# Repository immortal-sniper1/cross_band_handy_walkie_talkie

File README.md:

# Cross Band Handy Walkie Talkie

A Cross band handy walkie talkie: This HT would include 2 SA818s, one for 70cm and one for 2m and could be used for satellite work.
 
We recommend to install the following libraries:

__Audio__

- https://github.com/pschatzmann/arduino-audio-tools.git
- https://github.com/pschatzmann/arduino-audiokit.git (ES8388 driver for AudioKitStream class)
- https://github.com/thaaraak/es8388 (alternative ES8388 driver)
 
__DRA818__

To use the Transceiver you need an Arduino library. e.g.
- https://github.com/fatpat/arduino-dra818.git

 You can install this project as Arduino Library. To compile a Sketch select the __ESP32S3 Dev Module__ as board.

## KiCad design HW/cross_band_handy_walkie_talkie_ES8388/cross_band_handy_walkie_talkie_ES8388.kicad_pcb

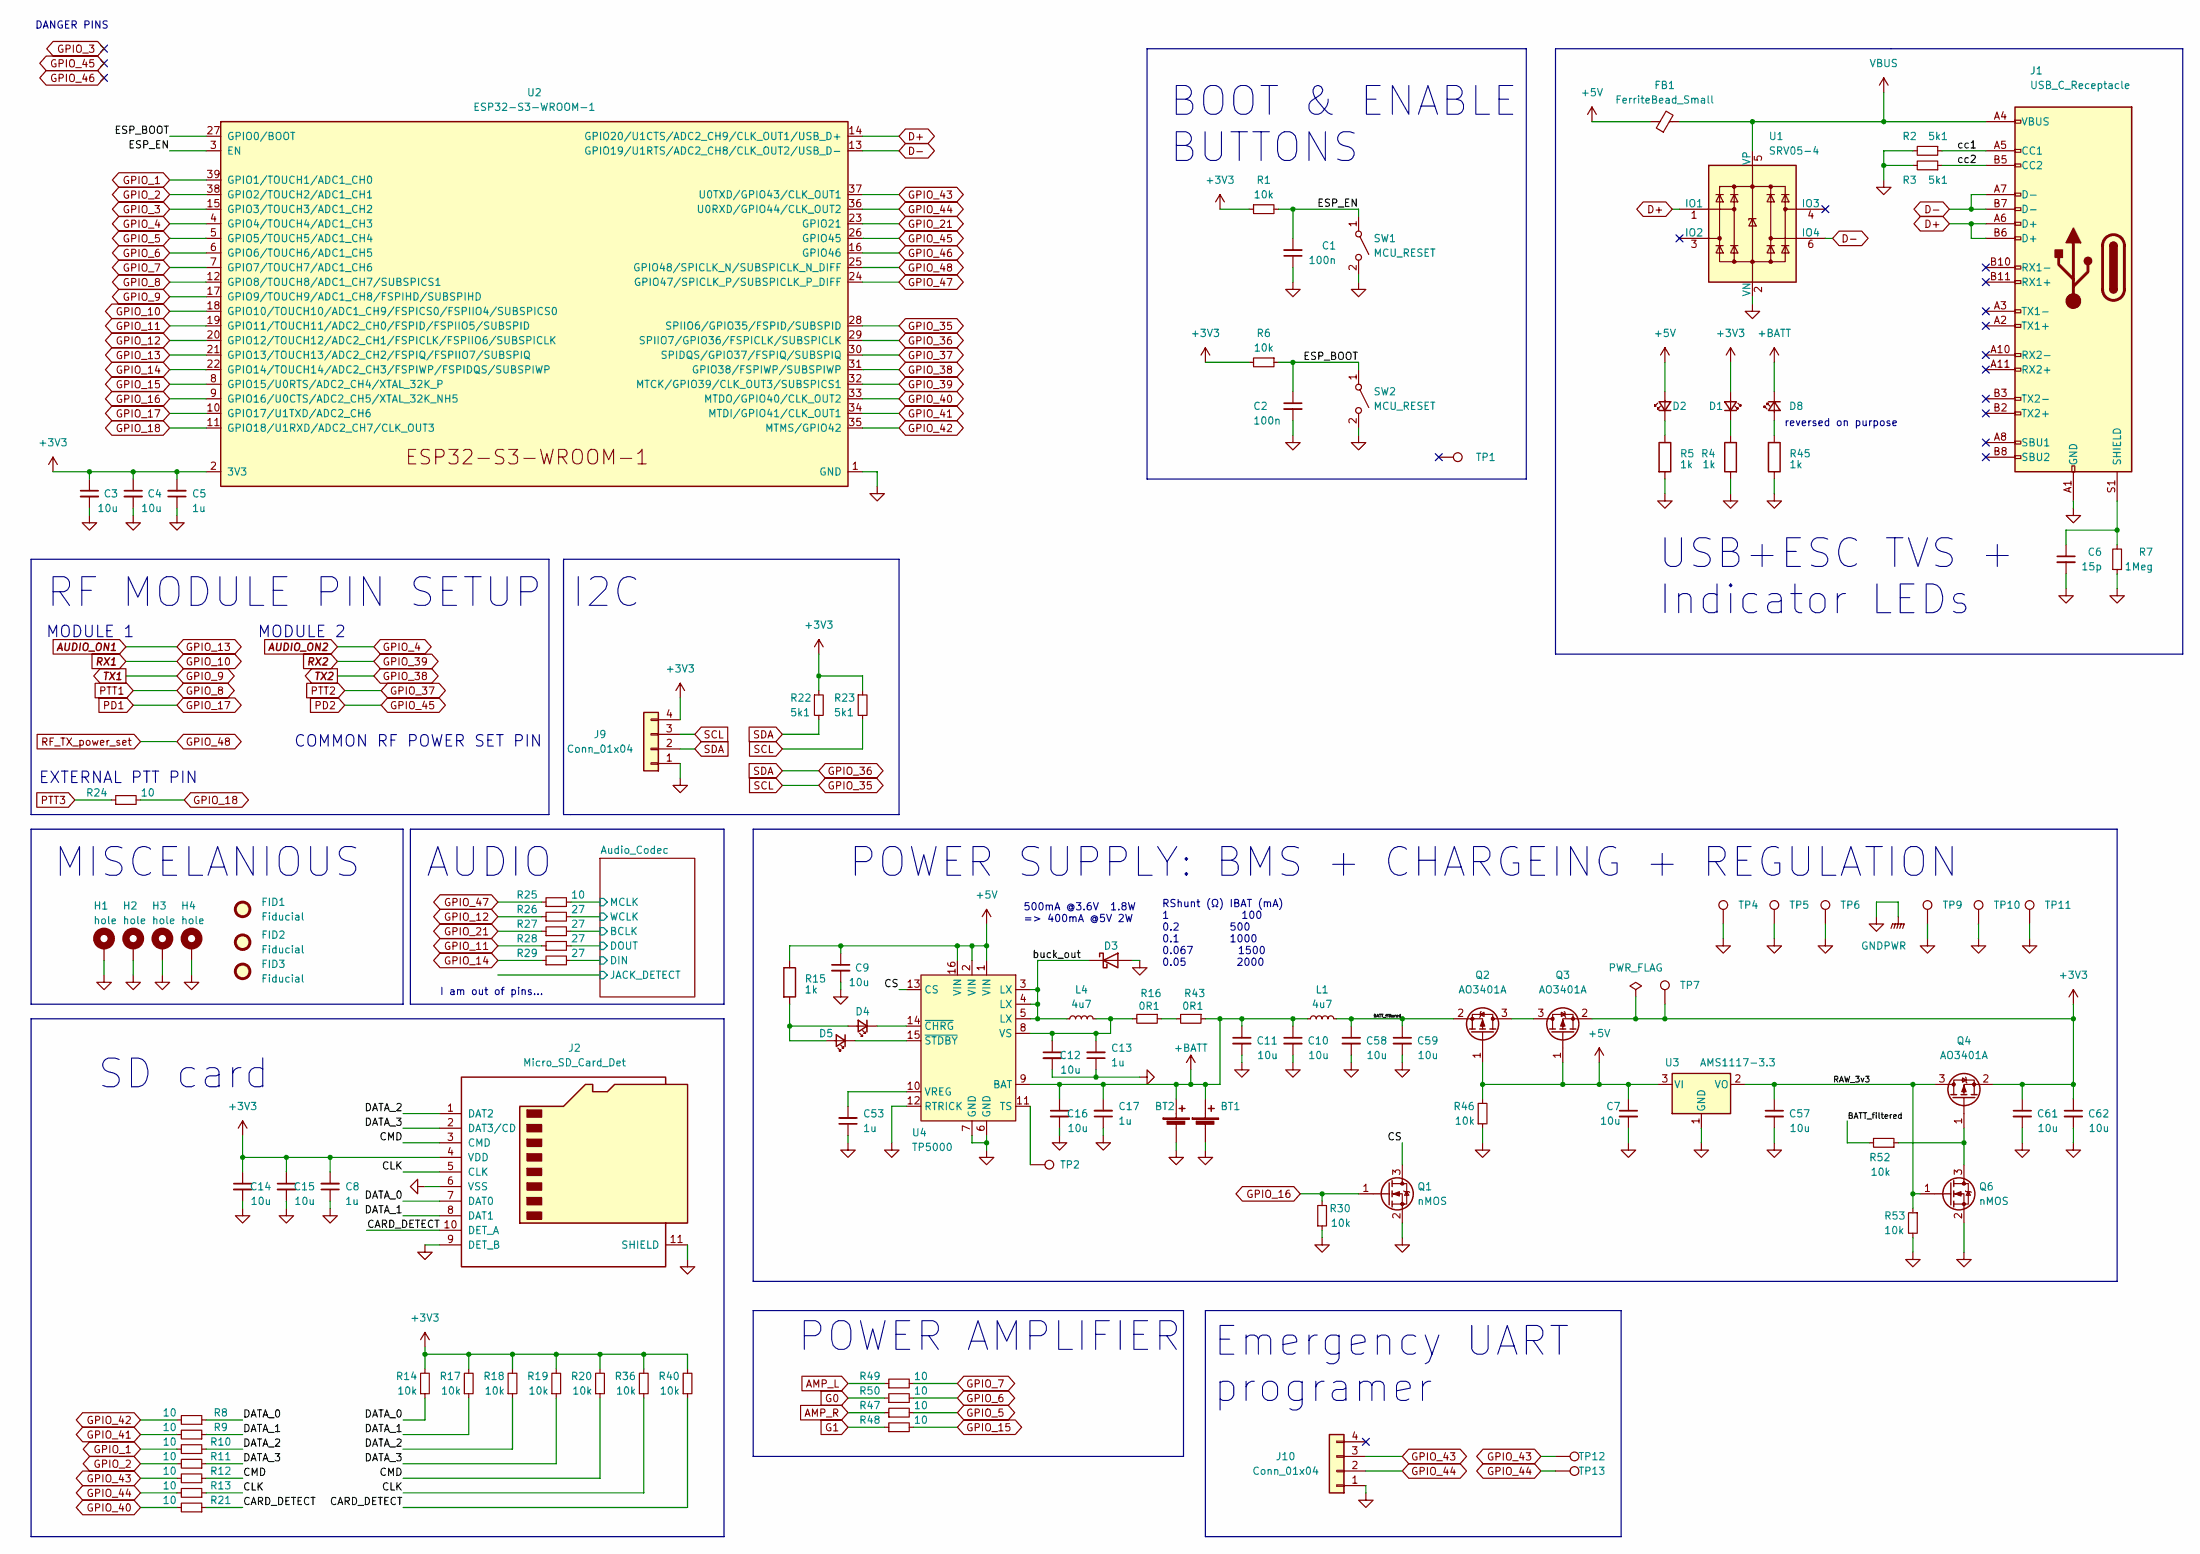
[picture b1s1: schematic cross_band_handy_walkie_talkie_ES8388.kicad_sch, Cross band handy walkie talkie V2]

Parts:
BT1: Battery_Cell; PinHeader_1x02_P2.54mm_Vertical
BT2: Battery_Cell; JST_XH_B2B-XH-AM_1x02_P2.50mm_Vertical
C1, C2: 100n; C_0603_1608Metric_Pad1.08x0.95mm_HandSolder; LCSC C14663
C3, C4, C7, C9, C10, C11, C12, C14, C15, C16, C57, C58, C59, C61, C62: 10u; C_0603_1608Metric; LCSC C96446
C5, C13, C17, C53: 1u; C_0402_1005Metric; LCSC C52923
C6: 15p; C_0603_1608Metric_Pad1.08x0.95mm_HandSolder; LCSC C1644
C8: 1u; C_0603_1608Metric_Pad1.08x0.95mm_HandSolder; LCSC C15849
D1, D2, D5: green; LED_0805_2012Metric; LCSC C2297
D3: D_Schottky; D_SMA_Handsoldering; LCSC C22452
D4, D8: red; LED_0603_1608Metric; LCSC C2286
FB1: FerriteBead_Small; R_0805_2012Metric; LCSC C1015
FID1: Fiducial; Fiducial_0.5mm_Mask1mm
FID2: Fiducial; KiCad-Logo2_5mm_SilkScreen
FID3: Fiducial; WEEE-Logo_4.2x6mm_SilkScreen
H1, H2, H3, H4: hole; MountingHole_3.2mm_M3_DIN965_Pad_TopBottom
J1: USB_C_Receptacle; USB_C_Receptacle_HRO_TYPE-C-31-M-12; LCSC C319148
J2: Micro_SD_Card_Det; microSD_HC_Molex_104031-0811; LCSC C585350
J9: Conn_01x04; PinHeader_1x04_P2.54mm_Vertical
J10: Conn_01x04; PinHeader_1x03_P2.54mm_Vertical
L1, L4: 4u7; Inductor_2.5x2x1.2mm; LCSC C3002553
Q1, Q6: nMOS; SOT-23; LCSC C8545
Q2, Q3, Q4: AO3401A; SOT-23; LCSC C15127
R1, R6, R30: 10k; R_0603_1608Metric_Pad0.98x0.95mm_HandSolder; LCSC C25804
R2, R3, R22, R23: 5k1; R_0402_1005Metric; LCSC C25905
R4, R5, R15: 1k; R_0805_2012Metric; LCSC C17513
R7: 1Meg; R_0603_1608Metric_Pad0.98x0.95mm_HandSolder; LCSC C22935
R8, R9, R10, R11, R12, R13, R21, R24, R25, R47, R48, R49, R50: 10; R_0402_1005Metric; LCSC C25077
R14, R17, R18, R19, R20, R36, R40, R46, R52, R53: 10k; R_0402_1005Metric; LCSC C25744
R16, R43: 0R1; R_1206_3216Metric; LCSC C25334
R26, R27, R28, R29: 27; R_0402_1005Metric; LCSC C25092
R45: 1k; R_0603_1608Metric; LCSC C21190
SW1, SW2: MCU_RESET; PTS526SK15SMTR2LFS; LCSC C318884
TP1, TP2, TP4, TP5, TP6, TP7, TP9, TP10, TP11, TP12, TP13: TestPoint; TestPoint_Pad_1.0x1.0mm
U1: SRV05-4; SOT-23-6; LCSC C85364
U2: ESP32-S3-WROOM-1; LCSC C2913204
U3: AMS1117-3.3; SOT-223-3_TabPin2; LCSC C6186
U4: TP5000; QFN-16-1EP_4x4mm_P0.65mm_EP2.5x2.5mm_ThermalVias; LCSC C51699

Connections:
+3V3: C3.1, C4.1, C5.2, C8.2, C14.1, C15.1, C61.1, C62.1, D1.2 (A), J2.4 (VDD), J9.4, Q3.2 (S), Q4.2 (S), R1.1, R6.2, R14.2, R17.2, R18.2, R19.2, R20.2, R22.1, R23.1, R36.2, R40.2, TP7.1, U2.2 (3V3); also elsewhere on the board
+5V: C7.1, C9.1, D2.2 (A), FB1.1, Q2.1 (G), Q3.1 (G), R15.1, R46.2, U3.3 (VI), U4.1 (VIN), U4.2 (VIN), U4.16 (VIN); also elsewhere on the board
+BATT: BT1.1 (+), BT2.1 (+), C10.1, C11.1, C16.1, C17.2, D8.1 (K), L1.1, R43.1, U4.9 (BAT)
/Audio_Codec/BCLK: R27.2; also elsewhere on the board
/Audio_Codec/DIN: R29.2; also elsewhere on the board
/Audio_Codec/DOUT: R28.2; also elsewhere on the board
/Audio_Codec/MCLK: R25.2; also elsewhere on the board
/Audio_Codec/WCLK: R26.2; also elsewhere on the board
/BATT_filtered: C58.1, C59.1, L1.2, Q2.2 (S), R52.2
/CARD_DETECT: J2.10 (DET_A), R21.1, R40.1
/CLK: J2.5 (CLK), R13.1, R36.1
/CMD: J2.3 (CMD), R12.1, R20.1
/CS: Q1.3 (D), U4.13 (CS)
/DATA_0: J2.7 (DAT0), R8.1, R14.1
/DATA_1: J2.8 (DAT1), R9.1, R17.1
/DATA_2: J2.1 (DAT2), R10.1, R18.1
/DATA_3: J2.2 (DAT3/CD), R11.1, R19.1
/ESP_BOOT: C2.1, R6.1, SW2.1 (A), U2.27 (GPIO0/BOOT)
/ESP_EN: C1.2, R1.2, SW1.1 (A), U2.3 (EN)
/RAW_3v3: C57.1, Q4.3 (D), Q6.1 (G), R53.1, U3.2 (VO)
/buck_out: D3.1 (K), L4.1, U4.3 (LX), U4.4 (LX), U4.5 (LX)
/cc1: J1.A5 (CC1), R2.1
/cc2: J1.B5 (CC2), R3.1
AMP_L: R49.1; also elsewhere on the board
AMP_R: R47.1; also elsewhere on the board
AUDIO_ON1: U2.21 (GPIO13/TOUCH13/ADC2_CH2/FSPIQ/FSPIIO7/S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); also elsewhere on the board
AUDIO_ON2: U2.4 (GPIO4/TOUCH4/ADC1_CH3); also elsewhere on the board
D+: J1.A6 (D+), J1.B6 (D+), U1.1 (IO1), U2.14 (GPIO20/U1CTS/ADC2_CH9/CLK_OUT1/USB_D+)
D-: J1.A7 (D-), J1.B7 (D-), U1.6 (IO4), U2.13 (GPIO19/U1RTS/ADC2_CH8/CLK_OUT2/USB_D-)
G0: R50.1; also elsewhere on the board
G1: R48.1; also elsewhere on the board
GND: BT1.2 (-), BT2.2 (-), C1.1, C2.2, C3.2, C4.2, C5.1, C6.2, C7.2, C8.1, C9.2, C10.2, C11.2, C12.2, C13.1, C14.2, C15.2, C16.2, C17.1, C53.1, C57.2, C58.2, C59.2, C61.2, C62.2, D3.2 (A), H1.1, H2.1, H3.1, H4.1, J1.A1 (GND), J1.A12 (GND), J1.B1 (GND), J1.B12 (GND), J2.6 (VSS), J2.9 (DET_B), J2.11 (SHIELD), J9.1, J10.1, Q1.2 (S), Q6.2 (S), R2.2, R3.2, R4.2, R5.2, R7.1, R30.1, R45.1, R46.1, R53.2, SW1.2 (B), SW2.2 (B), TP4.1, TP5.1, TP6.1, TP9.1, TP10.1, TP11.1, U1.2 (VN), U2.1 (GND), U2.40 (GND), U2.41 (GND), U3.1 (GND), U4.6 (GND), U4.7 (GND), U4.12 (RTRICK), U4.17 (PAD); also elsewhere on the board
GPIO_1: R10.2, U2.39 (GPIO1/TOUCH1/ADC1_CH0)
GPIO_2: R11.2, U2.38 (GPIO2/TOUCH2/ADC1_CH1)
GPIO_3: U2.15 (GPIO3/TOUCH3/ADC1_CH2)
GPIO_5: R47.2, U2.5 (GPIO5/TOUCH5/ADC1_CH4)
GPIO_6: R50.2, U2.6 (GPIO6/TOUCH6/ADC1_CH5)
GPIO_7: R49.2, U2.7 (GPIO7/TOUCH7/ADC1_CH6)
GPIO_8: U2.12 (GPIO8/TOUCH8/ADC1_CH7/SUBSPICS1); also elsewhere on the board
GPIO_9: U2.17 (GPIO9/TOUCH9/ADC1_CH8/FSPIHD/SUBSPIHD); also elsewhere on the board
GPIO_10: U2.18 (GPIO10/TOUCH10/ADC1_CH9/FSPICS0/FSPIIO4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); also elsewhere on the board
GPIO_11: R28.1, U2.19 (GPIO11/TOUCH11/ADC2_CH0/FSPID/FSPIIO5/S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)
GPIO_12: R26.1, U2.20 (GPIO12/TOUCH12/ADC2_CH1/FSPICLK/FSPIIO6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)
GPIO_14: R29.1, U2.22 (GPIO14/TOUCH14/ADC2_CH3/FSPIWP/FSPIDQS/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)
GPIO_15: R48.2, U2.8 (GPIO15/U0RTS/ADC2_CH4/XTAL_32K_P)
GPIO_16: Q1.1 (G), R30.2, U2.9 (GPIO16/U0CTS/ADC2_CH5/XTAL_32K_NH5)
GPIO_17: U2.10 (GPIO17/U1TXD/ADC2_CH6); also elsewhere on the board
GPIO_18: R24.2, U2.11 (GPIO18/U1RXD/ADC2_CH7/CLK_OUT3)
GPIO_21: R27.1, U2.23 (GPIO21)
GPIO_35: J9.3, R23.2, U2.28 (SPIIO6/GPIO35/FSPID/SUBSPID); also elsewhere on the board
GPIO_36: J9.2, R22.2, U2.29 (SPIIO7/GPIO36/FSPICLK/SUBSPICLK); also elsewhere on the board
GPIO_37: U2.30 (SPIDQS/GPIO37/FSPIQ/SUBSPIQ); also elsewhere on the board
GPIO_38: U2.31 (GPIO38/FSPIWP/SUBSPIWP); also elsewhere on the board
GPIO_39: U2.32 (MTCK/GPIO39/CLK_OUT3/SUBSPICS1); also elsewhere on the board
GPIO_40: R21.2, U2.33 (MTDO/GPIO40/CLK_OUT2)
GPIO_41: R9.2, U2.34 (MTDI/GPIO41/CLK_OUT1)
GPIO_42: R8.2, U2.35 (MTMS/GPIO42)
GPIO_43: J10.3, R12.2, TP12.1, U2.37 (U0TXD/GPIO43/CLK_OUT1)
GPIO_44: J10.2, R13.2, TP13.1, U2.36 (U0RXD/GPIO44/CLK_OUT2)
GPIO_45: U2.26 (GPIO45); also elsewhere on the board
GPIO_46: U2.16 (GPIO46)
GPIO_47: R25.1, U2.24 (GPIO47/SPICLK_P/SUBSPICLK_P_DIFF)
GPIO_48: U2.25 (GPIO48/SPICLK_N/SUBSPICLK_N_DIFF); also elsewhere on the board
unnamed: C6.1, J1.S1 (SHIELD), R7.2
unnamed: C12.1, C13.2, L4.2, R16.2, U4.8 (VS)
unnamed: C53.2, U4.10 (VREG)
unnamed: D1.1 (K), R4.1
unnamed: D2.1 (K), R5.1
unnamed: D4.1 (K), U4.14 (~CHRG)
unnamed: D4.2 (A), D5.2 (A), R15.2
unnamed: D5.1 (K), U4.15 (~STDBY)
unnamed: D8.2 (A), R45.2
unnamed: Q2.3 (D), Q3.3 (D)
unnamed: Q4.1 (G), Q6.3 (D), R52.1
unnamed: R16.1, R43.2
unnamed: TP2.1, U4.11 (TS)
PTT3: R24.1; also elsewhere on the board
VBUS: FB1.2, J1.A4 (VBUS), J1.A9 (VBUS), J1.B4 (VBUS), J1.B9 (VBUS), U1.5 (VP)

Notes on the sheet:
I am out of pins...
POWER AMPLIFIER
COMMON RF POWER SET PIN
500mA @3.6V 1.8W => 400mA @5V 2W
Emergency UART programer
MODULE 1
MODULE 2
reversed on purpose
AUDIO
EXTERNAL PTT PIN
RF MODULE PIN SETUP
RShunt (Ω) IBAT (mA) 1 100 0.2 500 0.1 1000 0.067 1500 0.05 2000
USB+ESC TVS + Indicator LEDs
SD card
MISCELANIOUS
I2C
POWER SUPPLY: BMS + CHARGEING + REGULATION
DANGER PINS
BOOT & ENABLE BUTTONS

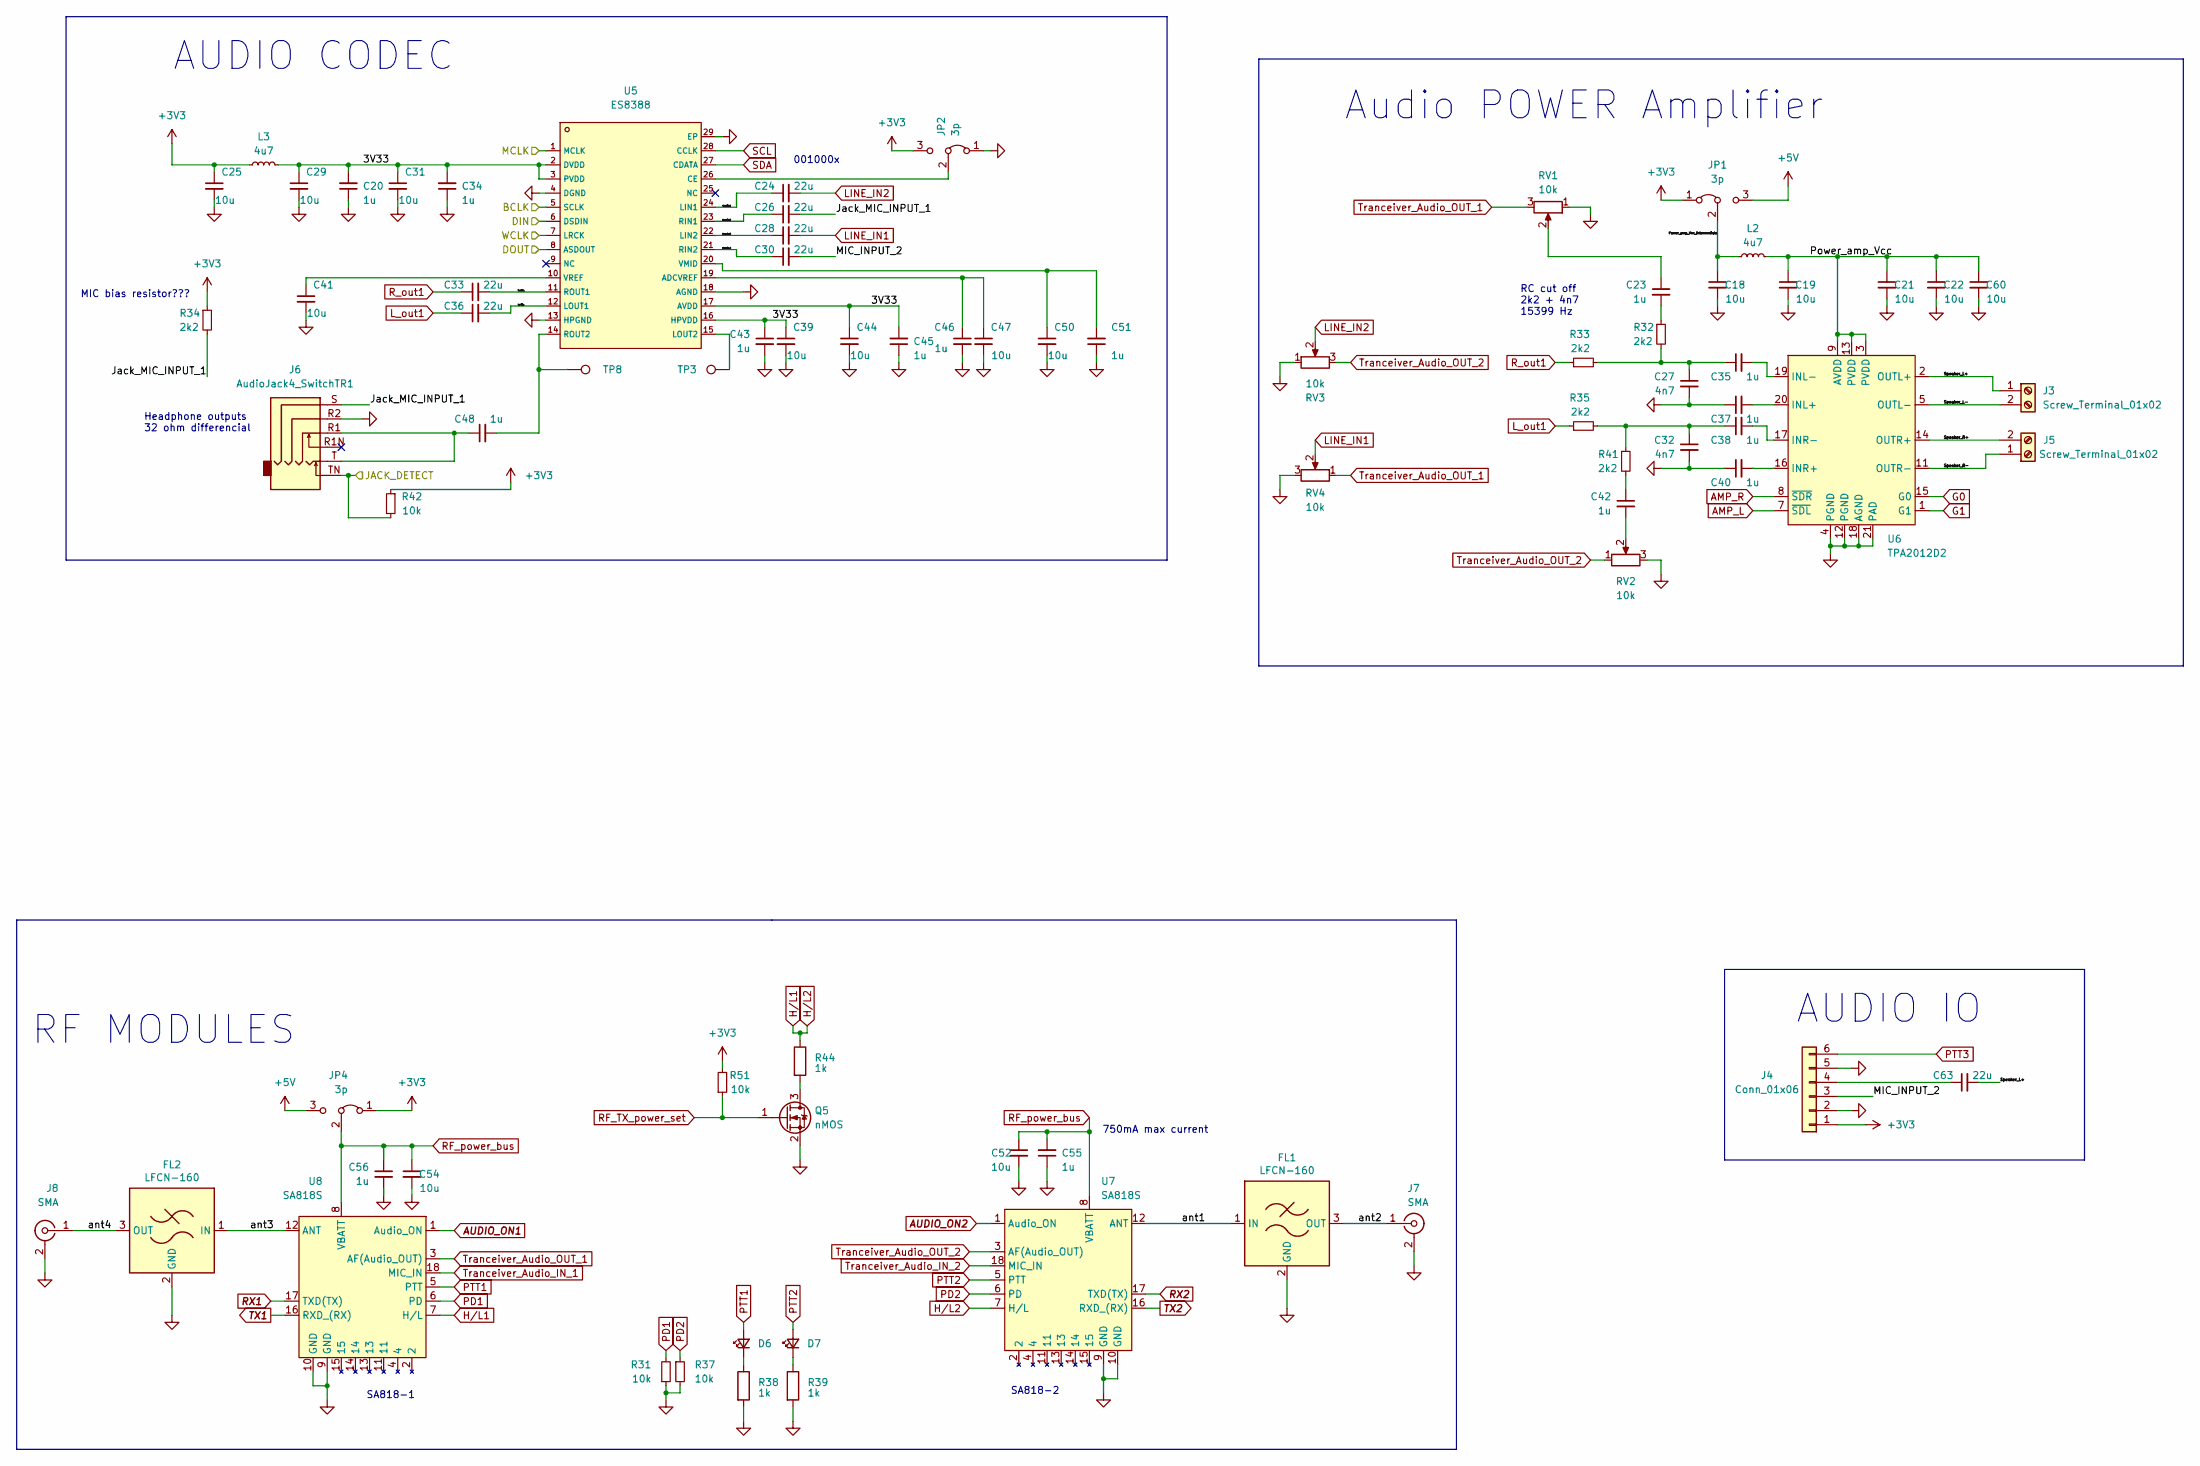
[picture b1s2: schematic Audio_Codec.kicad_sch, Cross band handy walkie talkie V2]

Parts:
C18, C19, C21, C22, C25, C29, C31, C39, C41, C44, C47, C50, C52, C54, C60: 10u; C_0603_1608Metric; LCSC C96446
C20, C23, C34, C35, C37, C38, C40, C42, C43, C45, C46, C51: 1u; C_0402_1005Metric; LCSC C52923
C24, C26, C28, C30, C33, C36, C63: 22u; C_0805_2012Metric; LCSC C45783
C27, C32: 4n7; C_0402_1005Metric; LCSC C1538
C48, C55, C56: 1u; C_0603_1608Metric_Pad1.08x0.95mm_HandSolder; LCSC C15849
D6, D7: red; LED_0603_1608Metric; LCSC C2286
FL1, FL2: LFCN-160; Filter_Mini-Circuits_FV1206
J3, J5: Screw_Terminal_01x02; Altech_AK300_1x02_P5.00mm_45-Degree
J4: Conn_01x06; PinHeader_1x06_P2.54mm_Vertical
J6: AudioJack4_SwitchTR1; PJ-316A-6A; LCSC C128987
J7, J8: SMA; SMA_Amphenol_901-144_Vertical
JP1, JP2, JP4: 3p; SolderJumper-3_P1.3mm_Bridged12_Pad1.0x1.5mm
L2, L3: 4u7; Inductor_2.5x2x1.2mm; LCSC C3002553
Q5: nMOS; SOT-23; LCSC C8545
R31, R37, R42, R51: 10k; R_0603_1608Metric_Pad0.98x0.95mm_HandSolder; LCSC C25804
R32, R33, R34, R35, R41: 2k2; R_0402_1005Metric; LCSC C25879
R38, R39, R44: 1k; R_0603_1608Metric; LCSC C21190
RV1, RV2, RV3, RV4: 10k; Potentiometer_Bourns_3314J_Vertical; LCSC C36376
TP3, TP8: TestPoint; TestPoint_Pad_1.0x1.0mm
U5: ES8388; QFN-28-1EP_4x4mm_P0.4mm_EP2.4x2.4mm_ThermalVias; LCSC C365736
U6: TPA2012D2; QFN-20-1EP_4x4mm_P0.5mm_EP2.6x2.6mm_ThermalVias; LCSC C7717
U7, U8: SA818S; LCSC C3001549

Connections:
+3V3: C25.1, J4.1, JP1.1 (A), JP2.3 (B), JP4.1 (A), L3.1, R34.1, R42.1, R51.2; also elsewhere on the board
+5V: JP1.3 (B), JP4.3 (B); also elsewhere on the board
/Audio_Codec/3V33: C20.2, C29.1, C31.1, C34.2, C39.1, C43.1, C44.1, C45.2, L3.2, U5.2 (DVDD), U5.3 (PVDD), U5.16 (HPVDD), U5.17 (AVDD)
/Audio_Codec/A_audio_1: C24.1, U5.24 (LIN1)
/Audio_Codec/A_audio_2: C26.1, U5.23 (RIN1)
/Audio_Codec/A_audio_3: C28.1, U5.22 (LIN2)
/Audio_Codec/A_audio_4: C30.1, U5.21 (RIN2)
/Audio_Codec/BCLK: U5.5 (SCLK); also elsewhere on the board
/Audio_Codec/DIN: U5.6 (DSDIN); also elsewhere on the board
/Audio_Codec/DOUT: U5.8 (ASDOUT); also elsewhere on the board
/Audio_Codec/JACK_DETECT: J6.TN, R42.2
/Audio_Codec/Jack_MIC_INPUT_1: C26.2, J6.S, R34.2
/Audio_Codec/L_out1_: C36.2, U5.12 (LOUT1)
/Audio_Codec/MCLK: U5.1 (MCLK); also elsewhere on the board
/Audio_Codec/MIC_INPUT_2: C30.2, J4.3
/Audio_Codec/Power_amp_Vcc: C19.1, C21.1, C22.1, C60.1, L2.2, U6.3 (PVDD), U6.9 (AVDD), U6.13 (PVDD)
/Audio_Codec/Power_amp_Vcc_intermediate: C18.1, JP1.2 (C), L2.1
/Audio_Codec/R_out1_: C33.2, U5.11 (ROUT1)
/Audio_Codec/Speaker_L+: C63.2, J3.1, U6.2 (OUTL+)
/Audio_Codec/Speaker_L-: J3.2, U6.5 (OUTL-)
/Audio_Codec/Speaker_R+: J5.2, U6.14 (OUTR+)
/Audio_Codec/Speaker_R-: J5.1, U6.11 (OUTR-)
/Audio_Codec/WCLK: U5.7 (LRCK); also elsewhere on the board
/Audio_Codec/ant1: FL1.1 (IN), U7.12 (ANT)
/Audio_Codec/ant2: FL1.3 (OUT), J7.1 (In)
/Audio_Codec/ant3: FL2.1 (IN), U8.12 (ANT)
/Audio_Codec/ant4: FL2.3 (OUT), J8.1 (In)
AMP_L: U6.7 (~SDL); also elsewhere on the board
AMP_R: U6.8 (~SDR); also elsewhere on the board
AUDIO_ON1: U8.1 (Audio_ON); also elsewhere on the board
AUDIO_ON2: U7.1 (Audio_ON); also elsewhere on the board
G0: U6.15 (G0); also elsewhere on the board
G1: U6.1 (G1); also elsewhere on the board
GND: C18.2, C19.2, C20.1, C21.2, C22.2, C25.2, C27.2, C29.2, C31.2, C32.2, C34.1, C37.1, C39.2, C40.1, C41.2, C43.2, C44.2, C45.1, C46.2, C47.2, C50.2, C51.1, C52.2, C54.2, C55.1, C56.2, C60.2, FL1.2 (GND), FL1.4 (GND), FL2.2 (GND), FL2.4 (GND), J4.2, J4.5, J6.R2, J7.2 (Ext), J8.2 (Ext), JP2.1 (A), Q5.2 (S), R31.1, R37.2, R38.2, R39.2, RV1.1, RV2.3, RV3.1, RV4.3, U5.4 (DGND), U5.13 (HPGND), U5.18 (AGND), U5.29 (EP), U6.4 (PGND), U6.12 (PGND), U6.18 (AGND), U6.21 (PAD), U7.9 (GND), U7.10 (GND), U8.9 (GND), U8.10 (GND); also elsewhere on the board
GPIO_8: D6.2 (A), U8.5 (PTT); also elsewhere on the board
GPIO_9: U8.16 (RXD_(RX)); also elsewhere on the board
GPIO_10: U8.17 (TXD(TX)); also elsewhere on the board
GPIO_17: R31.2, U8.6 (PD); also elsewhere on the board
GPIO_35: U5.28 (CCLK); also elsewhere on the board
GPIO_36: U5.27 (CDATA); also elsewhere on the board
GPIO_37: D7.2 (A), U7.5 (PTT); also elsewhere on the board
GPIO_38: U7.16 (RXD_(RX)); also elsewhere on the board
GPIO_39: U7.17 (TXD(TX)); also elsewhere on the board
GPIO_45: R37.1, U7.6 (PD); also elsewhere on the board
GPIO_48: Q5.1 (G), R51.1; also elsewhere on the board
H/L1: R44.1, U7.7 (H/L), U8.7 (H/L)
LINE_IN1: C28.2, RV4.2
LINE_IN2: C24.2, RV3.2
L_out1: C36.1, R35.1
unnamed: C23.1, RV1.2
unnamed: C23.2, R32.1
unnamed: C27.1, C35.1, R32.2, R33.2
unnamed: C32.1, C38.1, R35.2, R41.1
unnamed: C35.2, U6.19 (INL-)
unnamed: C37.2, U6.20 (INL+)
unnamed: C38.2, U6.17 (INR-)
unnamed: C40.2, U6.16 (INR+)
unnamed: C41.1, U5.10 (VREF)
unnamed: C42.1, R41.2
unnamed: C42.2, RV2.2
unnamed: C46.1, C47.1, U5.19 (ADCVREF)
unnamed: C48.1, J6.R1, J6.T
unnamed: C48.2, TP8.1, U5.14 (ROUT2)
unnamed: C50.1, C51.2, U5.20 (VMID)
unnamed: C63.1, J4.4
unnamed: D6.1 (K), R38.1
unnamed: D7.1 (K), R39.1
unnamed: JP2.2 (C), U5.26 (CE)
unnamed: Q5.3 (D), R44.2
unnamed: TP3.1, U5.15 (LOUT2)
PTT3: J4.6; also elsewhere on the board
RF_power_bus: C52.1, C54.1, C55.2, C56.1, JP4.2 (C), U7.8 (VBATT), U8.8 (VBATT)
R_out1: C33.1, R33.1
Tranceiver_Audio_IN_1: U8.18 (MIC_IN)
Tranceiver_Audio_IN_2: U7.18 (MIC_IN)
Tranceiver_Audio_OUT_1: RV1.3, RV4.1, U8.3 (AF(Audio_OUT))
Tranceiver_Audio_OUT_2: RV2.1, RV3.3, U7.3 (AF(Audio_OUT))

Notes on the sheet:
AUDIO IO
RC cut off 2k2 + 4n7 15399 Hz
SA818-1
Headphone outputs 32 ohm differencial
001000x
Audio POWER Amplifier
MIC bias resistor???
RF MODULES
750mA max current
AUDIO CODEC
SA818-2

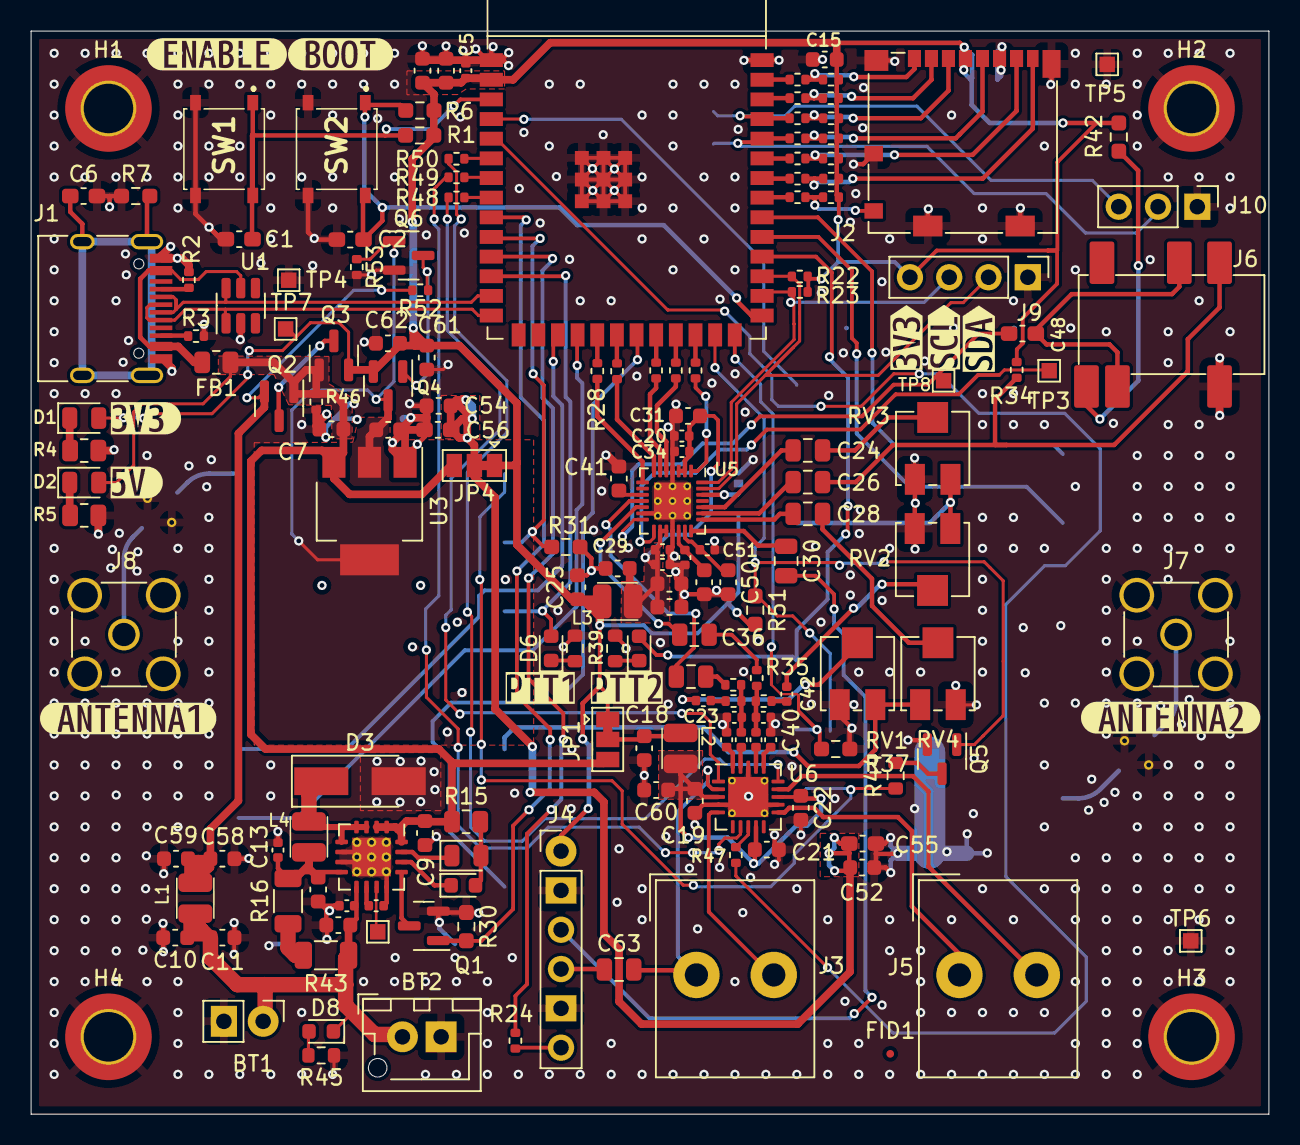
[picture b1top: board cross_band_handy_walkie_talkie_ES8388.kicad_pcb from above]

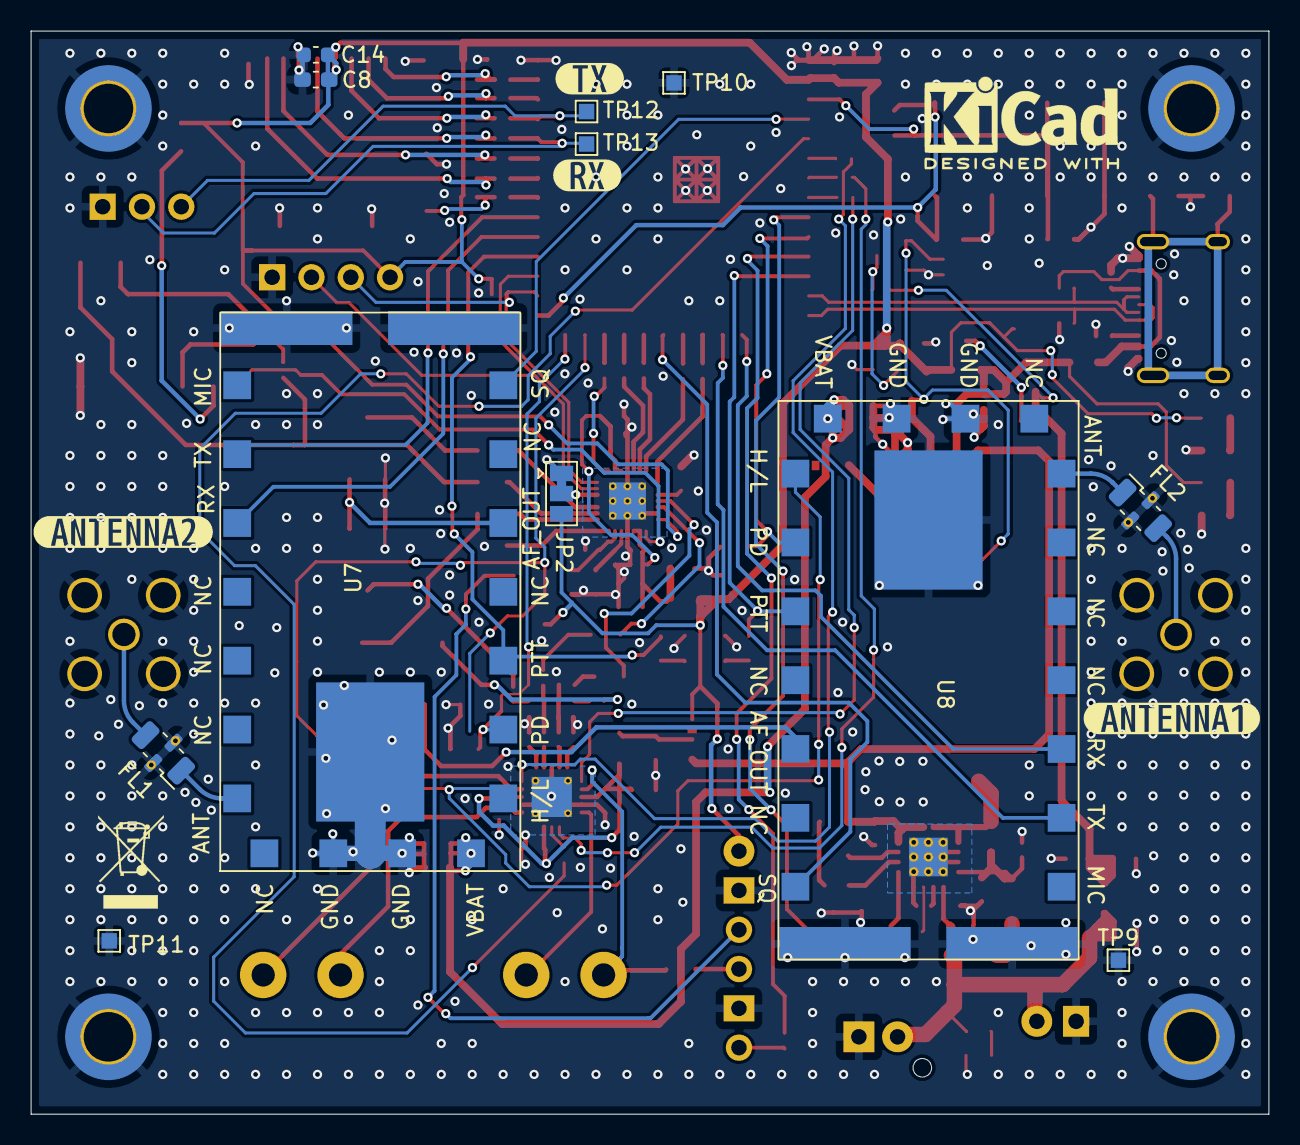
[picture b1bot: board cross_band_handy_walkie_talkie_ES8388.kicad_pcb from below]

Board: 4 copper layers, 80.0 x 70.0 mm, 199 parts (18 on the bottom side), 125 nets.

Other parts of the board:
kibuzzard-641A07F0: G***; kibuzzard-641A07F0
kibuzzard-641A0805: G***; kibuzzard-641A0805
kibuzzard-641B449E: G***; kibuzzard-641B449E
kibuzzard-641B4493: G***; kibuzzard-641B4493
kibuzzard-641EB0C1, kibuzzard-641EB0C1#2: G***; kibuzzard-641EB0C1
kibuzzard-641EB0D1, kibuzzard-641EB0D1#2: G***; kibuzzard-641EB0D1
kibuzzard-641EB1A6: G***; kibuzzard-641EB1A6
kibuzzard-641EB1B1: G***; kibuzzard-641EB1B1
kibuzzard-641EB11F: G***; kibuzzard-641EB11F
kibuzzard-641EB058: G***; kibuzzard-641EB058
kibuzzard-641EB069: G***; kibuzzard-641EB069
kibuzzard-641EB116: G***; kibuzzard-641EB116
kibuzzard-641EB161: G***; kibuzzard-641EB161

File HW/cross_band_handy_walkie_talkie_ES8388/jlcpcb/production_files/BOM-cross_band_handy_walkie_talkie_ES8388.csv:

Comment,Designator,Footprint,LCSC
FerriteBead_Small,FB1,R_0805_2012Metric,C1015
AudioJack4_SwitchTR1,J6,PJ-316A-6A,C128987
100n,"C1,C2",C_0603_1608Metric_Pad1.08x0.95mm_HandSolder,C14663
AO3401A,"Q2,Q3,Q4",SOT-23,C15127
4n7,"C27,C32",C_0402_1005Metric,C1538
1u,"C48,C55,C56,C8",C_0603_1608Metric_Pad1.08x0.95mm_HandSolder,C15849
15p,C6,C_0603_1608Metric_Pad1.08x0.95mm_HandSolder,C1644
1k,"R15,R4,R5",R_0805_2012Metric,C17513
1k,"R38,R39,R44,R45",R_0603_1608Metric,C21190
D_Schottky,D3,D_SMA_Handsoldering,C22452
red,"D4,D6,D7,D8",LED_0603_1608Metric,C2286
1Meg,R7,R_0603_1608Metric_Pad0.98x0.95mm_HandSolder,C22935
green,"D1,D2,D5",LED_0805_2012Metric,C2297
10,"R10,R11,R12,R13,R21,R24,R25,R47,R48,R49,R50,R8,R9",R_0402_1005Metric,C25077
27,"R26,R27,R28,R29",R_0402_1005Metric,C25092
0R1,"R16,R43",R_1206_3216Metric,C25334
10k,"R14,R17,R18,R19,R20,R36,R40,R46,R52,R53",R_0402_1005Metric,C25744
10k,"R1,R30,R31,R37,R42,R51,R6",R_0603_1608Metric_Pad0.98x0.95mm_HandSolder,C25804
2k2,"R32,R33,R34,R35,R41",R_0402_1005Metric,C25879
5k1,"R2,R22,R23,R3",R_0402_1005Metric,C25905
ESP32-S3-WROOM-1,U2,ESP32-S3-WROOM-1,C2913204
SA818S,"U7,U8",SA818S,C3001549
4u7,"L1,L2,L3,L4",Inductor_2.5x2x1.2mm,C3002553
MCU_RESET,"SW1,SW2",PTS526SK15SMTR2LFS,C318884
USB_C_Receptacle,J1,USB_C_Receptacle_HRO_TYPE-C-31-M-12,C319148
10k,"RV1,RV2,RV3,RV4",Potentiometer_Bourns_3314J_Vertical,C36376
ES8388,U5,QFN-28-1EP_4x4mm_P0.4mm_EP2.4x2.4mm_ThermalVias,C365736
22u,"C24,C26,C28,C30,C33,C36,C63",C_0805_2012Metric,C45783
TP5000,U4,QFN-16-1EP_4x4mm_P0.65mm_EP2.5x2.5mm_ThermalVias,C51699
1u,"C13,C17,C20,C23,C34,C35,C37,C38,C40,C42,C43,C45,C46,C5,C51,C53",C_0402_1005Metric,C52923
Micro_SD_Card_Det,J2,microSD_HC_Molex_104031-0811,C585350
AMS1117-3.3,U3,SOT-223-3_TabPin2,C6186
TPA2012D2,U6,QFN-20-1EP_4x4mm_P0.5mm_EP2.6x2.6mm_ThermalVias,C7717
SRV05-4,U1,SOT-23-6,C85364
nMOS,"Q1,Q5,Q6",SOT-23,C8545
10u,"C10,C11,C12,C14,C15,C16,C18,C19,C21,C22,C25,C29,C3,C31,C39,C4,C41,C44,C47,C50,C52,C54,C57,C58,C59,C60,C61,C62,C7,C9",C_0603_1608Metric,C96446
Screw_Terminal_01x02,J5,Altech_AK300_1x02_P5.00mm_45-Degree,
SMA,J7,SMA_Amphenol_901-144_Vertical,
SMA,J8,SMA_Amphenol_901-144_Vertical,
Screw_Terminal_01x02,J3,Altech_AK300_1x02_P5.00mm_45-Degree,
LFCN-160,FL2,Filter_Mini-Circuits_FV1206,
LFCN-160,FL1,Filter_Mini-Circuits_FV1206,
